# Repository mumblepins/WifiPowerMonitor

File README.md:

# Particle power monitor

Uses the [Particle](http://particle.io) Photon by default, but probably would work with a Core or one of the other Particle type devices.

Interfaces with a ST STPM34 ADC power-monitoring front-end and is designed for 2 CTs and 2 voltage inputs.  Resistors are sized in general for a 100A → 50mA current transformer, and 120V (US) voltage source.  Unlike the [OpenEnergyMonitor](https://openenergymonitor.org/emon/), we're using a seperate 24-bit ADC, and no voltage transformer. 

###License
#### Hardware
<br />This work is licensed under a <a rel="license" href="http://creativecommons.org/licenses/by-sa/4.0/">Creative Commons Attribution-ShareAlike 4.0 International License</a>.

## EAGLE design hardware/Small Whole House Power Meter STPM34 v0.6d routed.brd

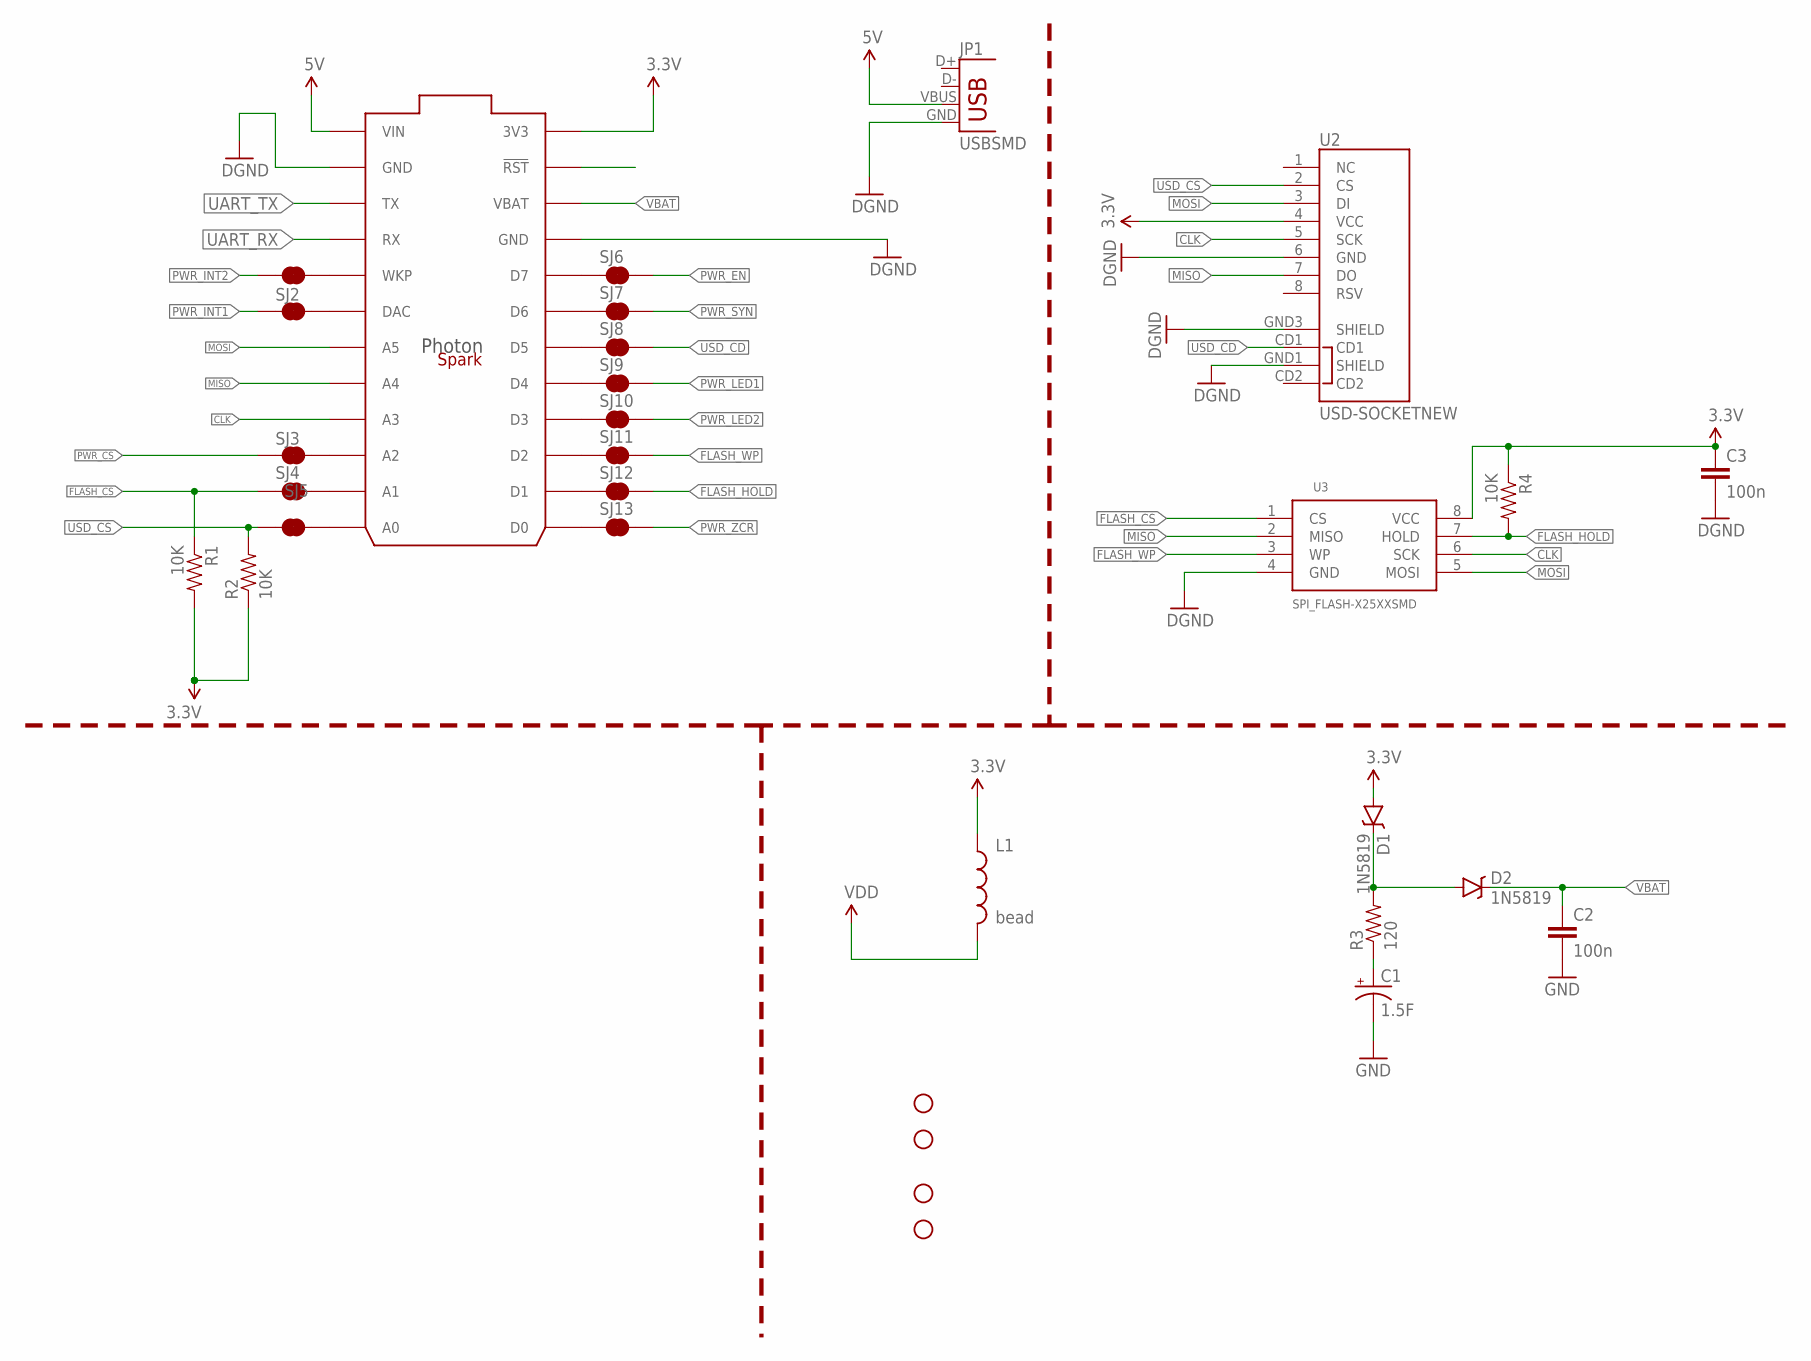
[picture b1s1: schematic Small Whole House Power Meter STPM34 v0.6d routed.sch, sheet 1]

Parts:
C1: 1.5F; 1.5SUPERCAPHORIZ
C2, C3: 100n; 0603-CAP
D1, D2: 1N5819; SOD-123
JP1: USBSMD; USB-MINIB
L1: bead; 0603
M1: SPARK_LOGO..; SPARK_LOGO
R1, R2, R4: 10K; 0603-RES
R3: 120; 0603-RES
SJ1, SJ2, SJ3, SJ4, SJ5, SJ6, SJ7, SJ8, SJ9, SJ10, SJ11, SJ12, SJ13: JUMPER-PAD-2-NC_BY_TRACE; PAD-JUMPER-2-NC_BY_TRACE_YES_SILK
STANDOFF1, STANDOFF2, STANDOFF3, STANDOFF4: STAND-OFF
U1: PHOTON_SMD_W_PINS
U2: USD-SOCKETNEW; MICRO-SD-SOCKET-PP
U3: SPI_FLASH-X25XXSMD; SO08N/W

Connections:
3.3V: C3.1, D1.A, L1.1, R1.2, R2.1, R4.1, U1.1_24 (3V3), U1.24 (3V3), U1.24* (3V3), U1.24_ (3V3), U2.4 (VCC), U3.8 (VCC)
5V: JP1.VBUS, U1.1 (VIN), U1.1* (VIN), U1.1_ (VIN), U1.1_1 (VIN)
CLK: U1.1_9 (A3), U1.9 (A3), U1.9* (A3), U1.9_ (A3), U2.5 (SCK), U3.6 (SCK); also elsewhere on the board
FLASH_CS: R1.1, SJ4.1, U3.1 (CS)
FLASH_HOLD: R4.2, SJ12.2, U3.7 (HOLD)
FLASH_WP: SJ11.2, U3.3 (WP)
GND: C1.-, C2.2, C3.2, JP1.GND, U1.1_2 (GND), U1.1_21 (GND), U1.2 (GND), U1.2* (GND), U1.2_ (GND), U1.21 (GND), U1.21* (GND), U1.21_ (GND), U2.6 (GND), U2.GND1 (SHIELD), U2.GND3 (SHIELD), U3.4 (GND); also elsewhere on the board
MISO: U1.1_8 (A4), U1.8 (A4), U1.8* (A4), U1.8_ (A4), U2.7 (DO), U3.2 (MISO); also elsewhere on the board
MOSI: U1.1_7 (A5), U1.7 (A5), U1.7* (A5), U1.7_ (A5), U2.3 (DI), U3.5 (MOSI); also elsewhere on the board
unnamed: SJ13.1, U1.1_13 (D0), U1.13 (D0), U1.13* (D0), U1.13_ (D0)
unnamed: U1.1_23 (!RST), U1.23 (!RST), U1.23* (!RST), U1.23_ (!RST)
unnamed: C1.+, R3.1
unnamed: SJ11.1, U1.1_15 (D2), U1.15 (D2), U1.15* (D2), U1.15_ (D2)
unnamed: SJ4.2, U1.1_11 (A1), U1.11 (A1), U1.11* (A1), U1.11_ (A1)
unnamed: SJ3.2, U1.1_10 (A2), U1.10 (A2), U1.10* (A2), U1.10_ (A2)
unnamed: SJ2.2, U1.1_6 (DAC), U1.6 (DAC), U1.6* (DAC), U1.6_ (DAC)
unnamed: SJ1.2, U1.1_5 (WKP), U1.5 (WKP), U1.5* (WKP), U1.5_ (WKP)
unnamed: SJ6.1, U1.1_20 (D7), U1.20 (D7), U1.20* (D7), U1.20_ (D7)
unnamed: SJ7.1, U1.1_19 (D6), U1.19 (D6), U1.19* (D6), U1.19_ (D6)
unnamed: SJ8.1, U1.1_18 (D5), U1.18 (D5), U1.18* (D5), U1.18_ (D5)
unnamed: SJ9.1, U1.1_17 (D4), U1.17 (D4), U1.17* (D4), U1.17_ (D4)
unnamed: SJ12.1, U1.1_14 (D1), U1.14 (D1), U1.14* (D1), U1.14_ (D1)
unnamed: SJ10.1, U1.1_16 (D3), U1.16 (D3), U1.16* (D3), U1.16_ (D3)
unnamed: D1.C, D2.A, R3.2
unnamed: SJ5.2, U1.1_12 (A0), U1.12 (A0), U1.12* (A0), U1.12_ (A0)
PWR_CS: SJ3.1; also elsewhere on the board
PWR_EN: SJ6.2; also elsewhere on the board
PWR_INT1: SJ2.1; also elsewhere on the board
PWR_INT2: SJ1.1; also elsewhere on the board
PWR_LED1: SJ9.2; also elsewhere on the board
PWR_LED2: SJ10.2; also elsewhere on the board
PWR_SYN: SJ7.2; also elsewhere on the board
PWR_ZCR: SJ13.2; also elsewhere on the board
UART_RX: U1.1_4 (RX), U1.4 (RX), U1.4* (RX), U1.4_ (RX)
UART_TX: U1.1_3 (TX), U1.3 (TX), U1.3* (TX), U1.3_ (TX)
USD_CD: SJ8.2, U2.CD1
USD_CS: R2.2, SJ5.1, U2.2 (CS)
VBAT: C2.1, D2.C, U1.1_22 (VBAT), U1.22 (VBAT), U1.22* (VBAT), U1.22_ (VBAT)
VDD: L1.2; also elsewhere on the board

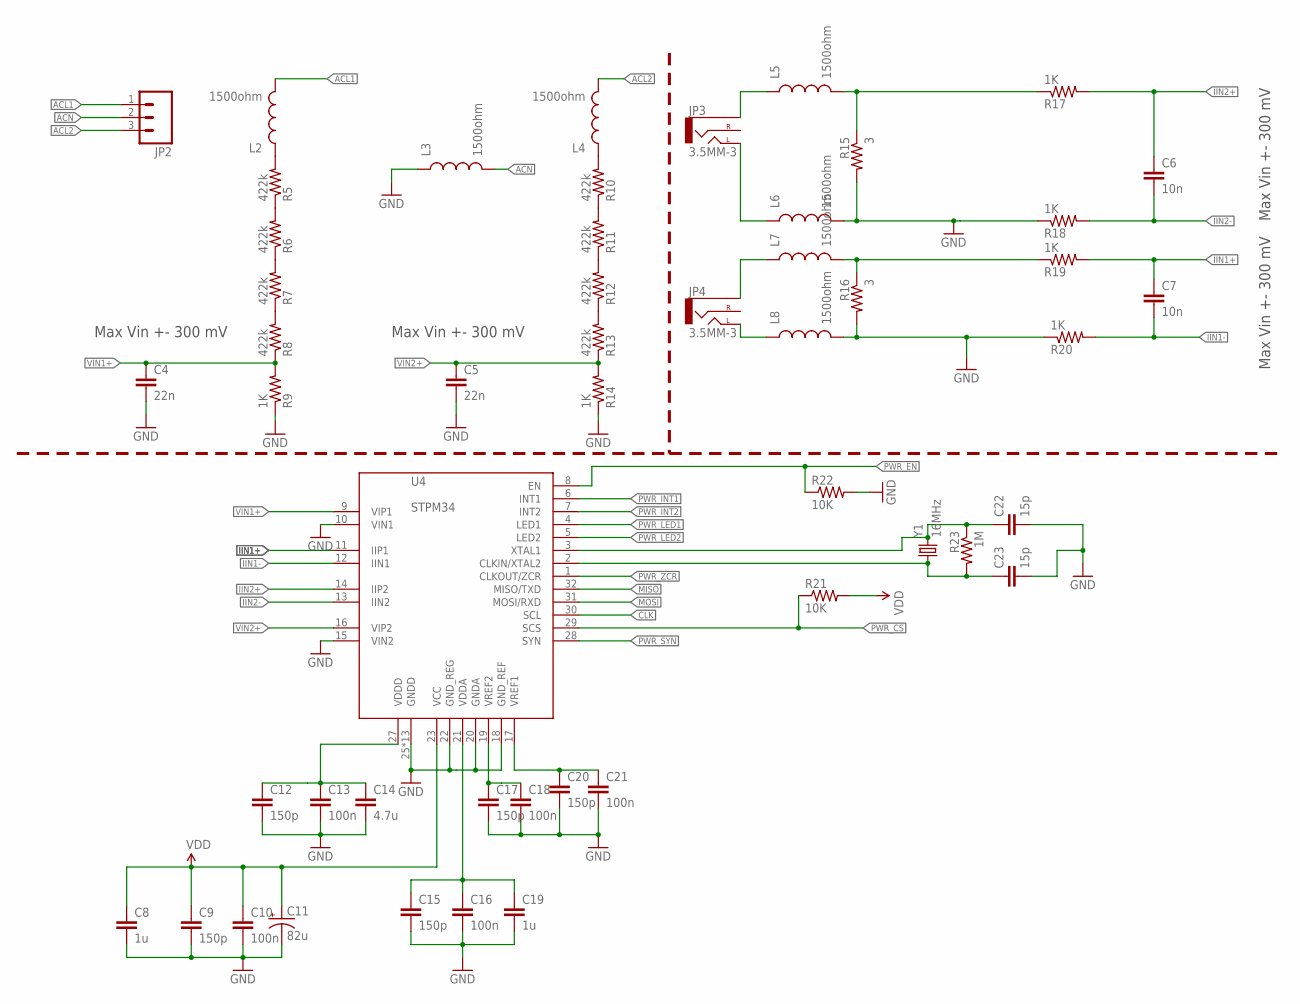
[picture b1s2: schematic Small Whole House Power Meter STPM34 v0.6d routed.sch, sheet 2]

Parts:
C4, C5: 22n; 0603-CAP
C6, C7: 10n; 0603-CAP
C8, C19: 1u; 0603-CAP
C9, C12, C15, C17, C20: 150p; 0603-CAP
C10, C13, C16, C18, C21: 100n; 0603-CAP
C11: 82u; CPOL-RADIAL-10UF-25V
C14: 4.7u; 0805
C22, C23: 15p; 0603-CAP
JP2: M03-SCREW-5MM; SCREWTERMINAL-5MM-3
JP3, JP4: 3.5MM-3; AUDIO-JACK
L2, L3, L4, L5, L6, L7, L8: 1500ohm; 0603
R5, R6, R7, R8, R10, R11, R12, R13: 422k; 1206
R9, R14, R17, R18, R19, R20: 1K; 0603-RES
R15, R16: 3; 0805
R21, R22: 10K; 0603-RES
R23: 1M; 0603-RES
U4: STPM34; UFQFPN32
Y1: 16MHz; HC49US

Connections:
ACL1: JP2.1, L2.2
ACL2: JP2.3, L4.2
ACN: JP2.2, L3.2
CLK: U4.30 (SCL); also elsewhere on the board
CUR_TRAN1+: L7.2, R16.1, R19.1
CUR_TRAN2+: L5.2, R15.1, R17.1
GND: C4.2, C5.2, C8.2, C9.2, C10.2, C11.2 (-), C12.2, C13.2, C14.2, C15.2, C16.2, C17.2, C18.2, C19.2, C20.2, C21.2, C22.2, C23.2, L3.1, L6.2, L8.2, R9.1, R14.1, R15.2, R16.2, R18.1, R20.1, R22.2, U4.10 (VIN1), U4.15 (VIN2), U4.18 (GND_REF), U4.20 (GNDA), U4.22 (GND_REG), U4.25 (GNDD), U4.26 (GNDD), U4.EXP (GNDD), U4.EXP1 (GNDD), U4.P$1 (GNDD), U4.P$2 (GNDD), U4.P$3 (GNDD), U4.P$4 (GNDD), U4.P$5 (GNDD), U4.P$6 (GNDD), U4.P$7 (GNDD), U4.P$8 (GNDD), U4.P$9 (GNDD); also elsewhere on the board
IIN1+: C7.1, R19.2, U4.11 (IIP1)
IIN1-: C7.2, R20.2, U4.12 (IIN1)
IIN2+: C6.1, R17.2, U4.14 (IIP2)
IIN2-: C6.2, R18.2, U4.13 (IIN2)
MISO: U4.32 (MISO/TXD); also elsewhere on the board
MOSI: U4.31 (MOSI/RXD); also elsewhere on the board
unnamed: L2.1, R5.2
unnamed: L4.1, R10.2
unnamed: C20.1, C21.1, U4.17 (VREF1)
unnamed: C23.1, R23.2, U4.2 (CLKIN/XTAL2), Y1.1
unnamed: C22.1, R23.1, U4.3 (XTAL1), Y1.2
unnamed: C15.1, C16.1, C19.1, U4.21 (VDDA)
unnamed: R7.1, R8.2
unnamed: R6.1, R7.2
unnamed: R5.1, R6.2
unnamed: R12.1, R13.2
unnamed: R11.1, R12.2
unnamed: R10.1, R11.2
unnamed: C17.1, C18.1, U4.19 (VREF2)
unnamed: JP4.TIP (LEFT), L8.1
unnamed: JP3.TIP (LEFT), L6.1
unnamed: JP3.SLEEVE, L5.1
unnamed: JP4.SLEEVE, L7.1
unnamed: C12.1, C13.1, C14.1, U4.27 (VDDD)
PWR_CS: R21.1, U4.29 (SCS); also elsewhere on the board
PWR_EN: R22.1, U4.8 (EN); also elsewhere on the board
PWR_INT1: U4.6 (INT1); also elsewhere on the board
PWR_INT2: U4.7 (INT2); also elsewhere on the board
PWR_LED1: U4.4 (LED1); also elsewhere on the board
PWR_LED2: U4.5 (LED2); also elsewhere on the board
PWR_SYN: U4.28 (SYN); also elsewhere on the board
PWR_ZCR: U4.1 (CLKOUT/ZCR); also elsewhere on the board
VDD: C8.1, C9.1, C10.1, C11.1 (+), R21.2, U4.23 (VCC); also elsewhere on the board
VIN1+: C4.1, R8.1, R9.2, U4.9 (VIP1)
VIN2+: C5.1, R13.1, R14.2, U4.16 (VIP2)

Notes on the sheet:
Max Vin +- 300 mV

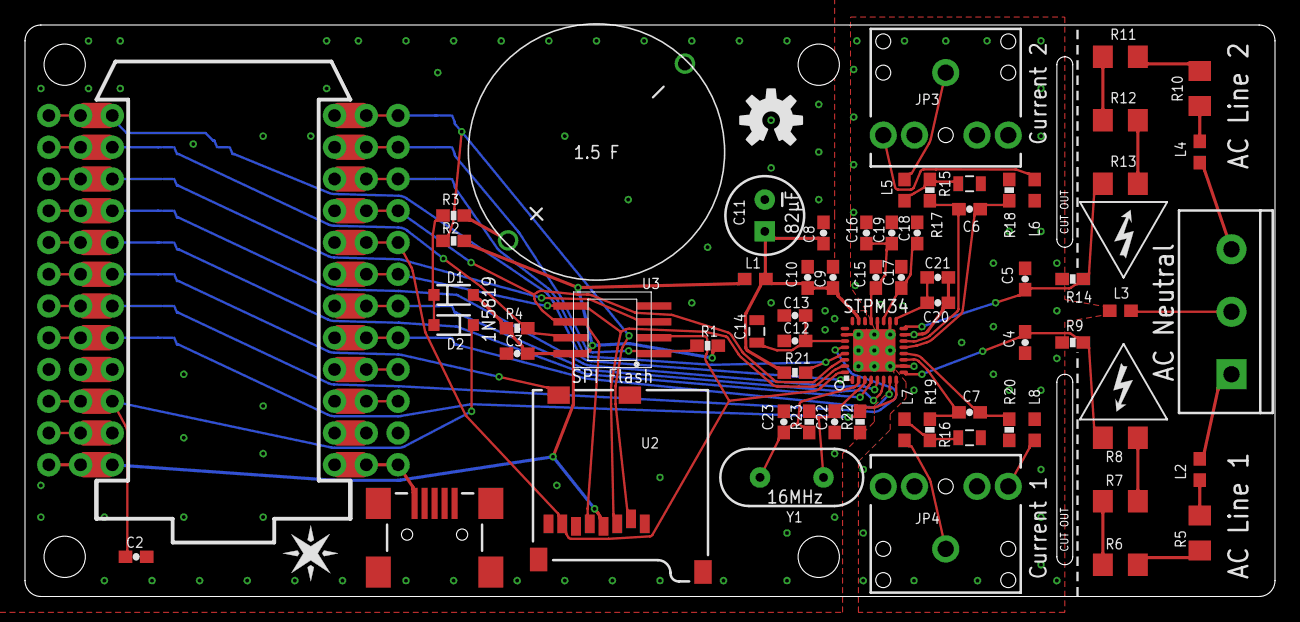
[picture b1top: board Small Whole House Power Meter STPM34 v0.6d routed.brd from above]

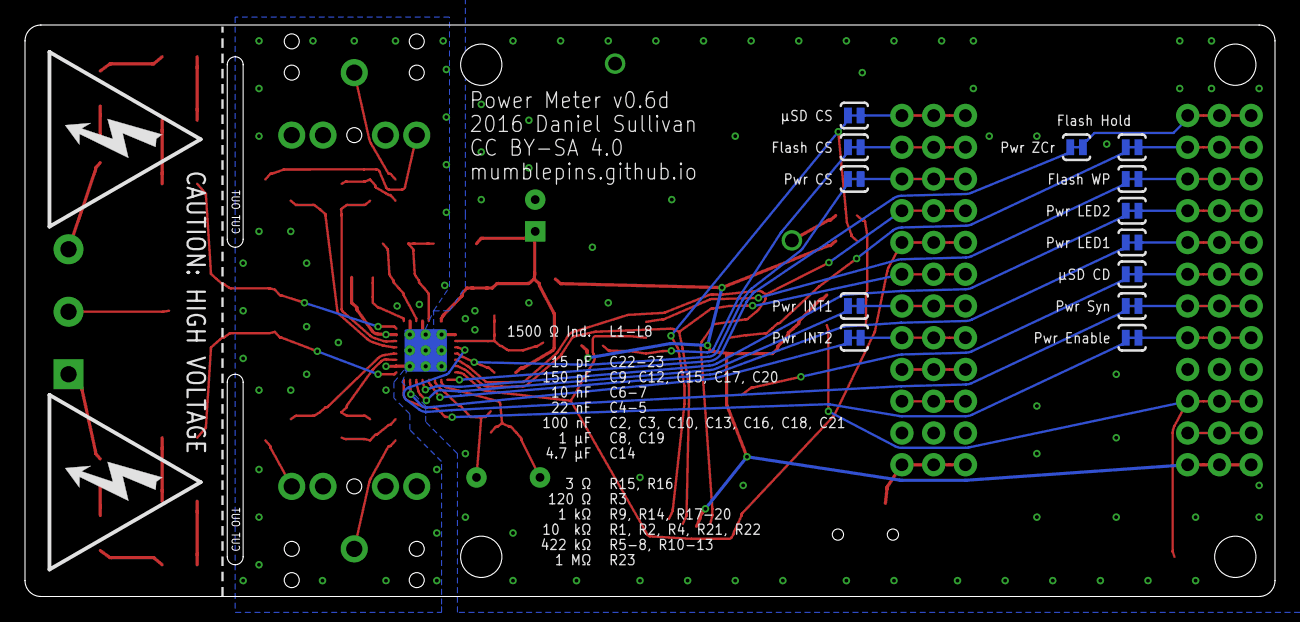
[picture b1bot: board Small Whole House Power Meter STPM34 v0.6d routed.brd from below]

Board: 2 copper layers, 100.0 x 45.7 mm, 88 parts (15 on the bottom side), 68 nets.

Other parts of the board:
E$1, E$5: HIGH_VOLTAGE
E$2, E$3: HIGH_VOLTAGE_HALF
E$4: OSHW-LOGO-M

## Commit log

2016-10-18 Added license

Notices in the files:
hardware/Small Whole House Power Meter STPM34 v0.6d routed.brd:
CC BY-SA 4.0
parts and their libraries:
SparkFun-Resistors: Licensing: Creative Commons ShareAlike 4.0 International - https://creativecommons.org/licenses/by-sa/4.0
